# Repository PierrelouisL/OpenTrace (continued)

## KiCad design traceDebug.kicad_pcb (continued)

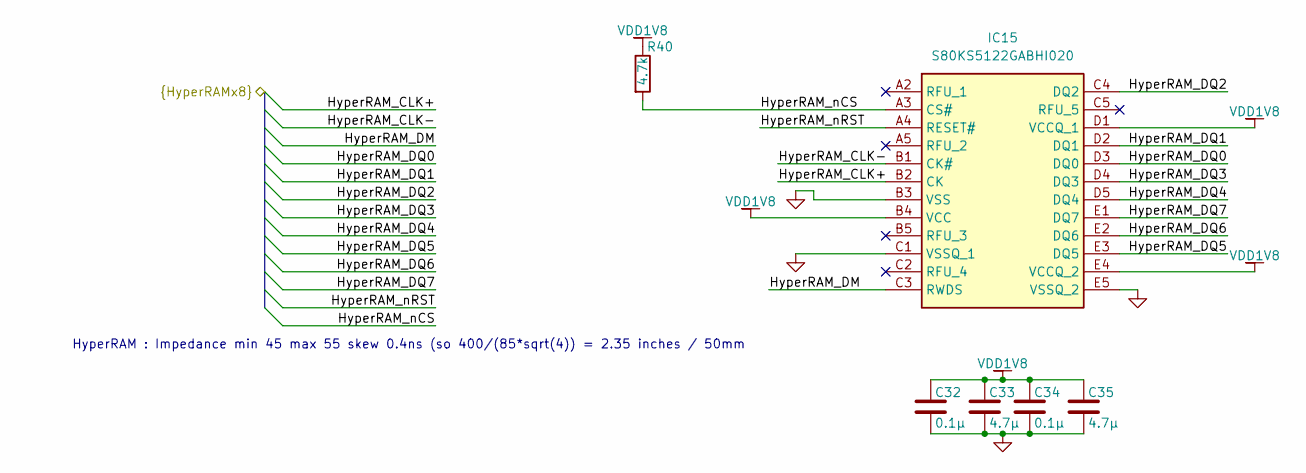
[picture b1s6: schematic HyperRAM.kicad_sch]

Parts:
C32, C34: 0.1µ; C_0402_1005Metric
C33, C35: 4.7µ; C_0402_1005Metric
IC15: S80KS5122GABHI020; BGA24C100P5X5_600X800X100; Manufacturer_Part_Number S80KS5122GABHI020; Mouser Part Number 727-S5122GABHI020
R40: 4.7k; R_0402_1005Metric

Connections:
/FPGA/HyperRAM_CLK+: IC15.B2 (CK); also elsewhere on the board
/FPGA/HyperRAM_CLK-: IC15.B1 (CK#); also elsewhere on the board
/FPGA/HyperRAM_DM: IC15.C3 (RWDS); also elsewhere on the board
/FPGA/HyperRAM_DQ0: IC15.D3 (DQ0); also elsewhere on the board
/FPGA/HyperRAM_DQ1: IC15.D2 (DQ1); also elsewhere on the board
/FPGA/HyperRAM_DQ2: IC15.C4 (DQ2); also elsewhere on the board
/FPGA/HyperRAM_DQ3: IC15.D4 (DQ3); also elsewhere on the board
/FPGA/HyperRAM_DQ4: IC15.D5 (DQ4); also elsewhere on the board
/FPGA/HyperRAM_DQ5: IC15.E3 (DQ5); also elsewhere on the board
/FPGA/HyperRAM_DQ6: IC15.E2 (DQ6); also elsewhere on the board
/FPGA/HyperRAM_DQ7: IC15.E1 (DQ7); also elsewhere on the board
/FPGA/HyperRAM_nCS: IC15.A3 (CS#), R40.2; also elsewhere on the board
/FPGA/HyperRAM_nRST: IC15.A4 (RESET#); also elsewhere on the board
GND: C32.2, C33.2, C34.2, C35.2, IC15.B3 (VSS), IC15.C1 (VSSQ_1), IC15.E5 (VSSQ_2); also elsewhere on the board
VDD1V8: C32.1, C33.1, C34.1, C35.1, IC15.B4 (VCC), IC15.D1 (VCCQ_1), IC15.E4 (VCCQ_2), R40.1; also elsewhere on the board

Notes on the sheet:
HyperRAM : Impedance min 45 max 55 skew 0.4ns (so 400/(85*sqrt(4)) = 2.35 inches / 50mm

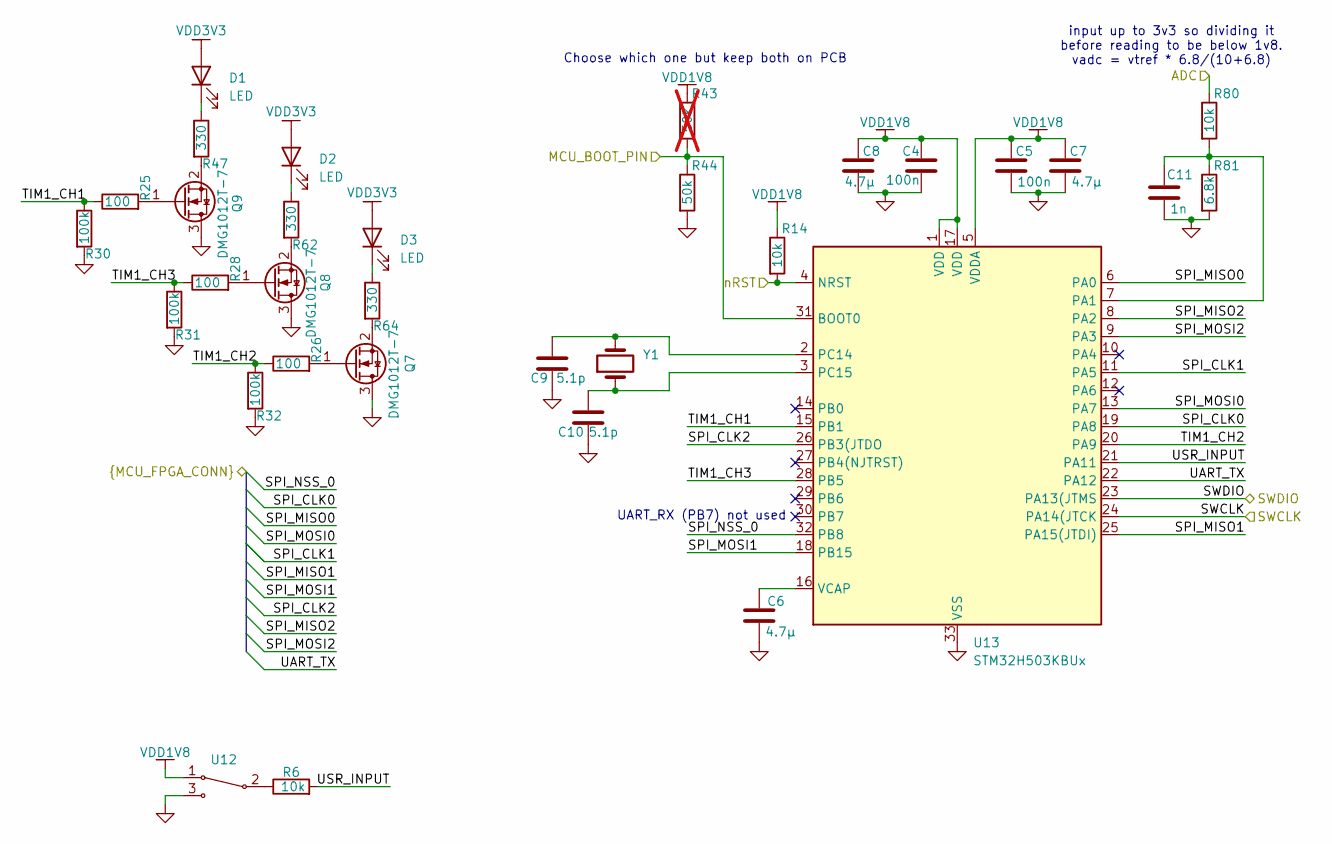
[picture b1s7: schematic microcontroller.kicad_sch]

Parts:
C4, C5: 100n; C_0402_1005Metric
C6, C7, C8: 4.7µ; C_0402_1005Metric
C9, C10: 5.1p; C_0402_1005Metric
C11: 1n; C_0402_1005Metric
D1, D2, D3: LED; D_0402_1005Metric
Q7, Q8, Q9: DMG1012T-7; SOT-523; LCSC C20512
R6, R14, R80: 10k; R_0402_1005Metric
R25, R26, R28: 100; R_0402_1005Metric
R30, R31, R32: 100k; R_0402_1005Metric
R43: 50k; R_0402_1005Metric; not fitted
R44: 50k; R_0402_1005Metric
R47, R62, R64: 330; R_0402_1005Metric
R81: 6.8k; R_0402_1005Metric
U12: C2906280
U13: STM32H503KBUx; QFN-32-1EP_5x5mm_P0.5mm_EP3.45x3.45mm
Y1: C19723454

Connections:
/DebugConnector/MCU_BOOT_PIN: R43.2, R44.1, U13.31 (BOOT0); also elsewhere on the board
/DebugConnector/SPI_CLK0: U13.19 (PA8); also elsewhere on the board
/DebugConnector/SPI_CLK1: U13.11 (PA5); also elsewhere on the board
/DebugConnector/SPI_CLK2: U13.26 (PB3(JTDO); also elsewhere on the board
/DebugConnector/SPI_MISO0: U13.6 (PA0); also elsewhere on the board
/DebugConnector/SPI_MISO1: U13.25 (PA15(JTDI)); also elsewhere on the board
/DebugConnector/SPI_MISO2: U13.8 (PA2); also elsewhere on the board
/DebugConnector/SPI_MOSI0: U13.13 (PA7); also elsewhere on the board
/DebugConnector/SPI_MOSI1: U13.18 (PB15); also elsewhere on the board
/DebugConnector/SPI_MOSI2: U13.9 (PA3); also elsewhere on the board
/DebugConnector/SPI_NSS_0: U13.32 (PB8); also elsewhere on the board
/DebugConnector/UART_TX: U13.22 (PA12); also elsewhere on the board
/DebugConnector/VTRef: R80.1; also elsewhere on the board
/DebugConnector/nRST: R14.2, U13.4 (NRST); also elsewhere on the board
/microcontroller/SWCLK: U13.24 (PA14(JTCK); also elsewhere on the board
/microcontroller/SWDIO: U13.23 (PA13(JTMS); also elsewhere on the board
/microcontroller/TIM1_CH1: R25.1, R30.1, U13.15 (PB1)
/microcontroller/TIM1_CH2: R26.1, R32.1, U13.20 (PA9)
/microcontroller/TIM1_CH3: R28.1, R31.1, U13.28 (PB5)
/microcontroller/USR_INPUT: R6.2, U13.21 (PA11)
GND: C4.2, C5.2, C6.2, C7.2, C8.2, C9.1, C10.1, C11.2, Q7.3 (D), Q8.3 (D), Q9.3 (D), R30.2, R31.2, R32.2, R44.2, R81.2, U12.3, U13.33 (VSS); also elsewhere on the board
unnamed: D1.1 (K), R47.1
unnamed: D2.1 (K), R62.1
unnamed: D3.1 (K), R64.1
unnamed: Q7.1 (G), R26.2
unnamed: Q7.2 (S), R64.2
unnamed: Q8.1 (G), R28.2
unnamed: Q8.2 (S), R62.2
unnamed: Q9.1 (G), R25.2
unnamed: Q9.2 (S), R47.2
unnamed: R6.1, U12.2
unnamed: C11.1, R80.2, R81.1, U13.7 (PA1)
unnamed: C9.2, U13.2 (PC14), Y1.2
unnamed: C10.2, U13.3 (PC15), Y1.1
unnamed: C6.1, U13.16 (VCAP)
VDD1V8: C4.1, C5.1, C7.1, C8.1, R14.1, R43.1, U12.1, U13.1 (VDD), U13.5 (VDDA), U13.17 (VDD); also elsewhere on the board
VDD3V3: D1.2 (A), D2.2 (A), D3.2 (A); also elsewhere on the board

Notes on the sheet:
Choose which one but keep both on PCB
UART_RX (PB7) not used
input up to 3v3 so dividing it before reading to be below 1v8. vadc = vtref * 6.8/(10+6.8)

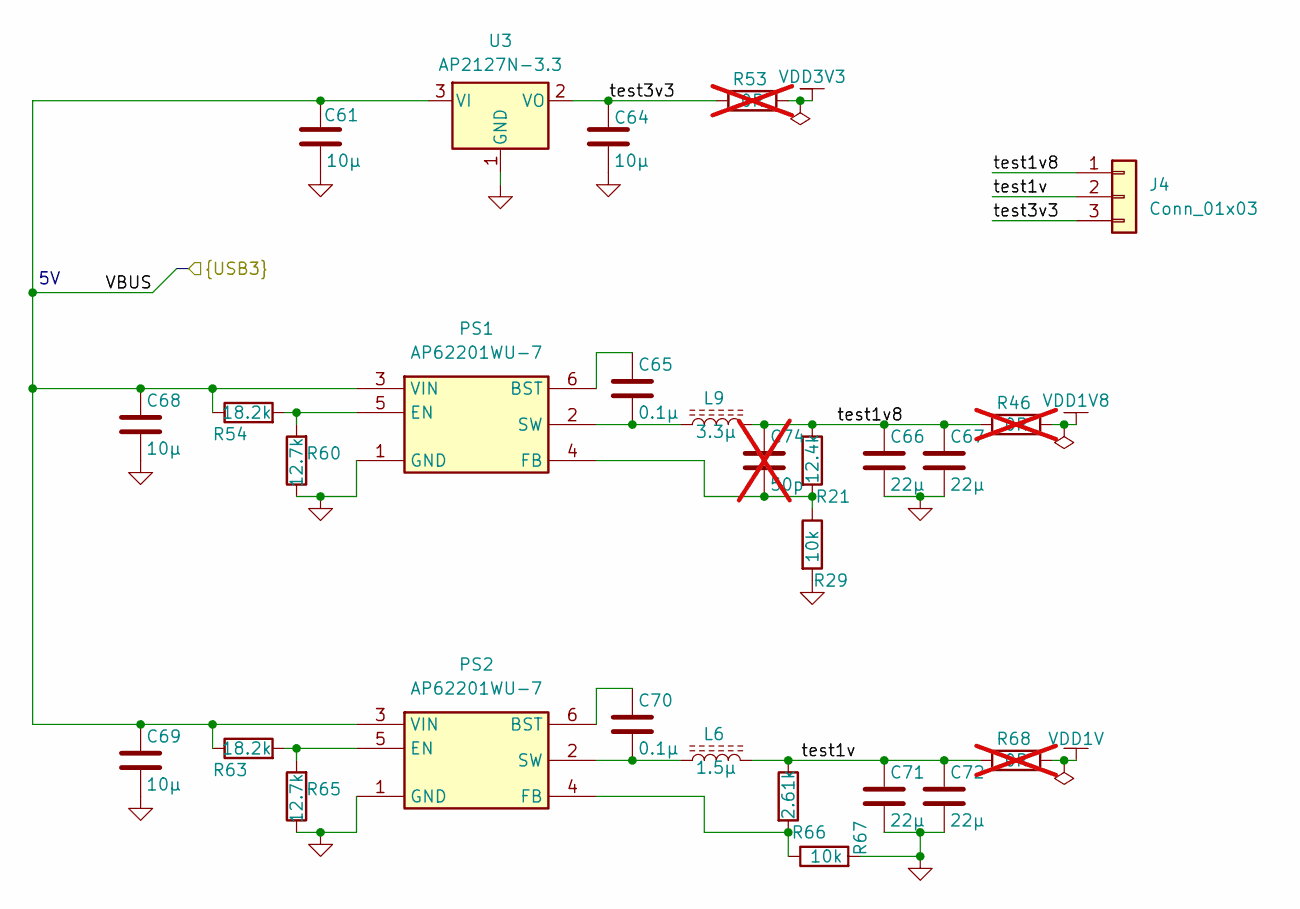
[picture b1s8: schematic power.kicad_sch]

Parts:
C61, C64, C68, C69: 10µ; C_0402_1005Metric
C65, C70: 0.1µ; C_0402_1005Metric
C66, C67, C71, C72: 22µ; C_0402_1005Metric
C74: 50p; C_0402_1005Metric; not fitted
J4: Conn_01x03; PinHeader_1x03_P2.54mm_Vertical
L6: 1.5µ; MTQH2016; LCSC C17701135
L9: 3.3µ; MTQH2016; LCSC C17701123
PS1, PS2: AP62201WU-7; SOT95P280X100-6N; Manufacturer_Part_Number AP62201WU-7; Mouser Part Number 621-AP62201WU-7
R21: 12.4k; R_0402_1005Metric
R29, R67: 10k; R_0402_1005Metric
R46, R68: 0R; R_0603_1608Metric; not fitted
R53: 0R; R_0402_1005Metric; not fitted
R54, R63: 18.2k; R_0402_1005Metric
R60, R65: 12.7k; R_0402_1005Metric
R66: 2.61k; R_0402_1005Metric
U3: AP2127N-3.3; SOT-23; LCSC C50314345

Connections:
/FPGA/VBUS: C61.1, C68.1, C69.1, PS1.3 (VIN), PS2.3 (VIN), R54.1, R63.1, U3.3 (VI); also elsewhere on the board
/Power/test1v: C71.1, C72.1, J4.2, L6.2, R66.1, R68.1
/Power/test1v8: C66.1, C67.1, C74.1, J4.1, L9.2, R21.1, R46.1
/Power/test3v3: C64.1, J4.3, R53.1, U3.2 (VO)
GND: C61.2, C64.2, C66.2, C67.2, C68.2, C69.2, C71.2, C72.2, PS1.1 (GND), PS2.1 (GND), R29.2, R60.1, R65.1, R67.2, U3.1 (GND); also elsewhere on the board
unnamed: C65.1, PS1.6 (BST)
unnamed: PS1.5 (EN), R54.2, R60.2
unnamed: C74.2, PS1.4 (FB), R21.2, R29.1
unnamed: C65.2, L9.1, PS1.2 (SW)
unnamed: C70.1, PS2.6 (BST)
unnamed: PS2.5 (EN), R63.2, R65.2
unnamed: PS2.4 (FB), R66.2, R67.1
unnamed: C70.2, L6.1, PS2.2 (SW)
VDD1V: R68.2; also elsewhere on the board
VDD1V8: R46.2; also elsewhere on the board
VDD3V3: R53.2; also elsewhere on the board

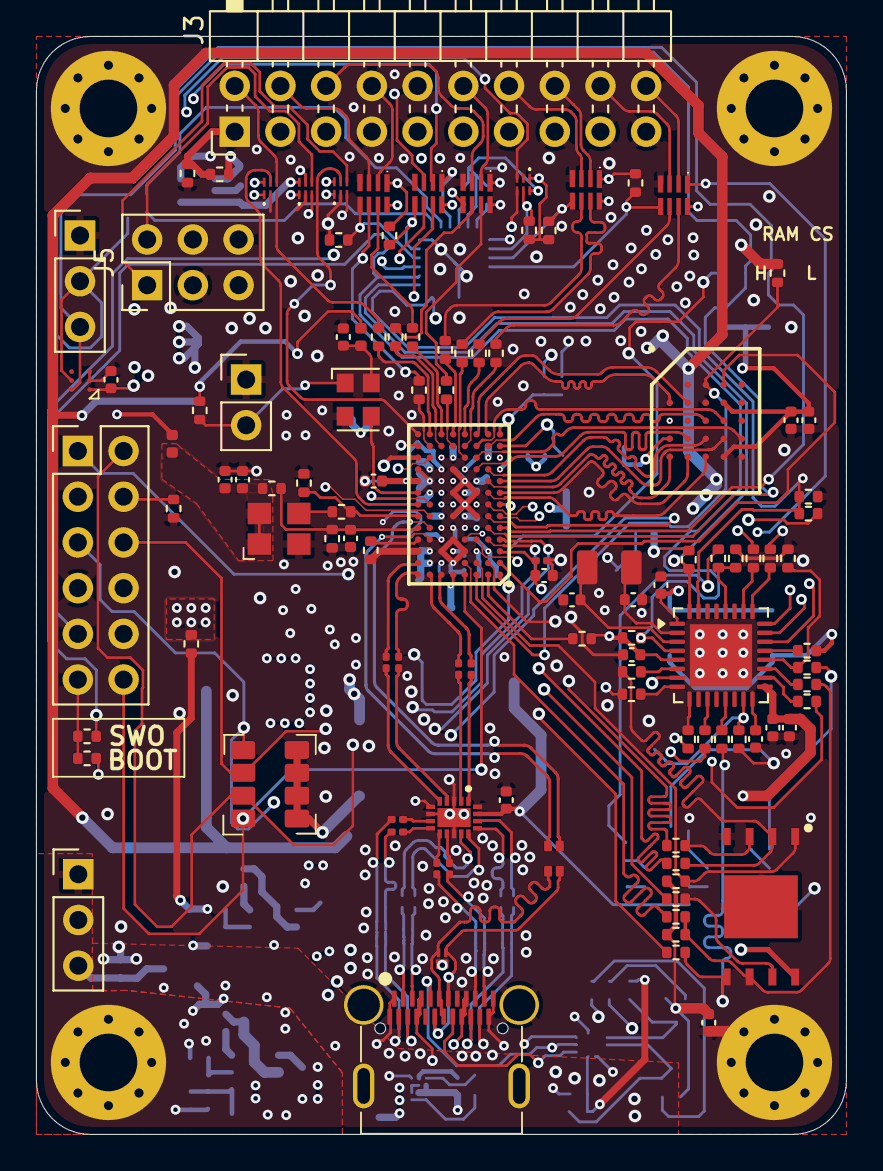
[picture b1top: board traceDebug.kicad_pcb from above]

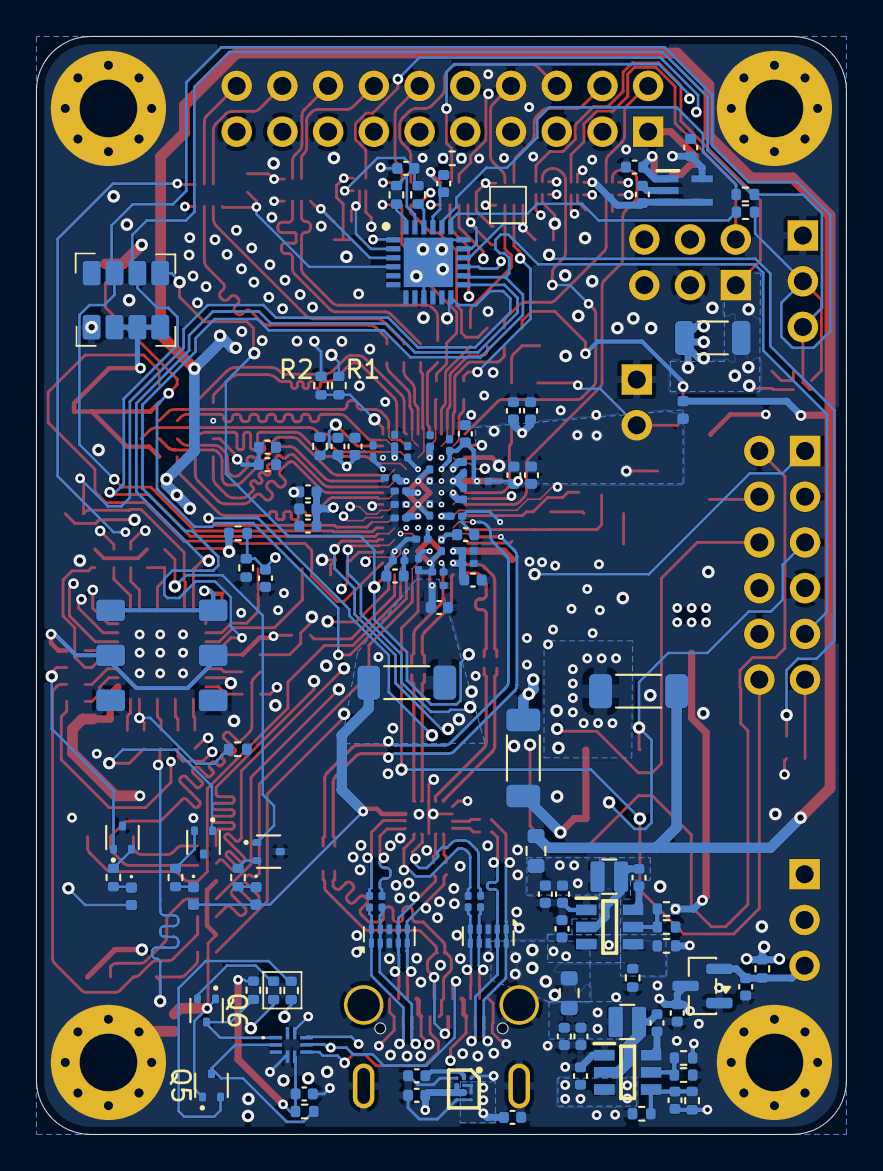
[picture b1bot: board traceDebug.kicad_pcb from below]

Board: 6 copper layers, 45.0 x 61.0 mm, 234 parts (119 on the bottom side), 196 nets.

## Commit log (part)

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2026-03-31 Pwr routing
